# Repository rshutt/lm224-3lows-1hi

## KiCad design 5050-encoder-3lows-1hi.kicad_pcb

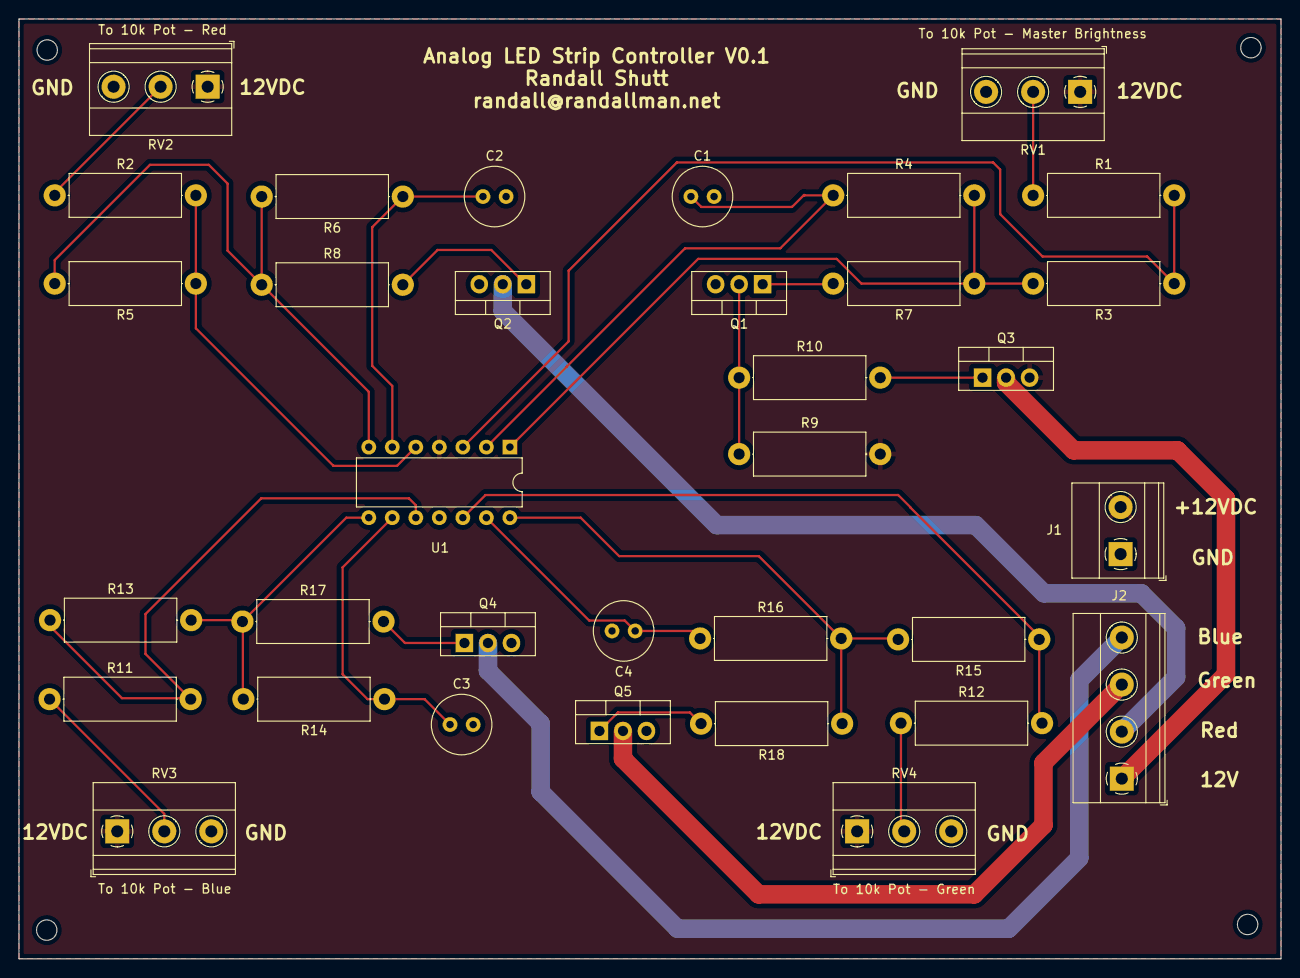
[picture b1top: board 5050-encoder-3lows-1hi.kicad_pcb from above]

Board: 2 copper layers, 136.3 x 101.5 mm, 38 parts (0 on the bottom side), 28 nets.

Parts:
C1, C2, C3, C4: 0.1uF; C_Radial_D6.3mm_H5.0mm_P2.50mm
H1, H2, H3, H4: MountingHole; MountingHole_2.2mm_M2
J1: Power; TerminalBlock_Phoenix_MKDS-1,5-2-5.08_1x02_P5.08mm_Horizont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
J2: To LEDs; TerminalBlock_Phoenix_MKDS-1,5-4-5.08_1x04_P5.08mm_Horizont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
Q1, Q2, Q4, Q5: IRLB8721; TO-220-3_Vertical
Q3: IRF5210L; TO-220-3_Vertical
R1, R2, R9, R11, R12: 1k; R_Axial_DIN0414_L11.9mm_D4.5mm_P15.24mm_Horizontal
R3, R5, R13, R15: 47k; R_Axial_DIN0414_L11.9mm_D4.5mm_P15.24mm_Horizontal
R4, R6, R14, R16: 10k; R_Axial_DIN0414_L11.9mm_D4.5mm_P15.24mm_Horizontal
R7, R8, R10, R17, R18: 330; R_Axial_DIN0414_L11.9mm_D4.5mm_P15.24mm_Horizontal
RV1: To 10k Pot - Master Brightness; TerminalBlock_Phoenix_MKDS-1,5-3-5.08_1x03_P5.08mm_Horizont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
RV2: To 10k Pot - Red; TerminalBlock_Phoenix_MKDS-1,5-3-5.08_1x03_P5.08mm_Horizont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
RV3: To 10k Pot - Blue; TerminalBlock_Phoenix_MKDS-1,5-3-5.08_1x03_P5.08mm_Horizont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
RV4: To 10k Pot - Green; TerminalBlock_Phoenix_MKDS-1,5-3-5.08_1x03_P5.08mm_Horizont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
U1: LM224; DIP-14_W7.62mm

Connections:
+12V: J1.2, Q3.3 (S), R9.2, RV1.1, RV2.1, RV3.1, RV4.1, U1.4 (Vcc)
GND: C1.2, C2.2, C3.2, C4.2, J1.1, Q1.3 (S), Q2.3 (S), Q4.3 (S), Q5.3 (S), RV1.3, RV2.3, RV3.3, RV4.3, U1.11 (GND)
unnamed: C1.1, R4.1, U1.2
unnamed: C2.1, R6.1, U1.6
unnamed: C3.1, R14.1, U1.9
unnamed: C4.1, R16.1, U1.13
unnamed: J2.1, Q3.2 (D)
unnamed: J2.2, Q2.2 (D)
unnamed: J2.3, Q5.2 (D)
unnamed: J2.4, Q4.2 (D)
unnamed: Q1.1 (G), R7.2
unnamed: Q1.2 (D), R9.1, R10.1
unnamed: Q2.1 (G), R8.2
unnamed: Q3.1 (G), R10.2
unnamed: Q4.1 (G), R17.2
unnamed: Q5.1 (G), R18.2
unnamed: R1.1, RV1.2
unnamed: R1.2, R3.1, U1.3
unnamed: R2.1, RV2.2
unnamed: R2.2, R5.1, U1.5
unnamed: R3.2, R4.2, R7.1, U1.1
unnamed: R5.2, R6.2, R8.1, U1.7
unnamed: R11.1, RV3.2
unnamed: R11.2, R13.1, U1.10
unnamed: R12.1, RV4.2
unnamed: R12.2, R15.1, U1.12
unnamed: R13.2, R14.2, R17.1, U1.8
unnamed: R15.2, R16.2, R18.1, U1.14

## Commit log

2022-02-22 Ok more stuff
2022-02-22 Removing old gerbers
2022-02-22 Ok this is another checkpoint
